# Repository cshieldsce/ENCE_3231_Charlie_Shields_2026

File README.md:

# Embedded Systems Coursework (ENCE 3231)

A small portfolio-style repo of my embedded + hardware design work for class.

## Projects

### 01 — Lab 1: Ultrasonic sensor (timers only)

- **Folder:** `01_lab1_ultrasonic_timers/`
- **What it shows:** timer-driven trigger pulse + measurement cycle; scope + block diagram.
- **Write-up:** `01_lab1_ultrasonic_timers/README.md`

### 02 — CAN board (KiCad)

- **Folder:** `02_can_kicad_board/`
- **What it shows:** CAN interface/board design in KiCad (schematic + PCB).
- **Write-up:** `02_can_kicad_board/README.md`

### 03 — Balancing robot schematic (KiCad)

- **Folder:** `03_balancing_robot_schematic_v1/`
- **What it shows:** system schematic for a 2-wheel balancing robot build.
- **Write-up:** `03_balancing_robot_schematic_v1/README.md`

### 04 — Balancing robot PCB layout (KiCad)

- **Folder:** `04_balancing_robot_pcb_v1/2026_12_2Wheel_Balance_Robot_v1/`
- **What it shows:** PCB layout + 3D renders for the balancing robot.
- **Write-up:** `04_balancing_robot_pcb_v1/README.md`

## Quick open / build

- **KiCad:** open the `*.kicad_pro` file inside a project folder.
- **STM32CubeIDE:** open/import the folder under the lab and build in the IDE (build outputs are ignored).

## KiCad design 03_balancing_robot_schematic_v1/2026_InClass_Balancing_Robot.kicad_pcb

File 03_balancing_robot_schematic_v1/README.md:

# 2-Wheel Balancing Robot — Schematic (v1)

## Open in KiCad

- Open `2026_InClass_Balancing_Robot.kicad_pro`

## Preview

## Export

- PDF: `docs/schematic_guide.pdf`

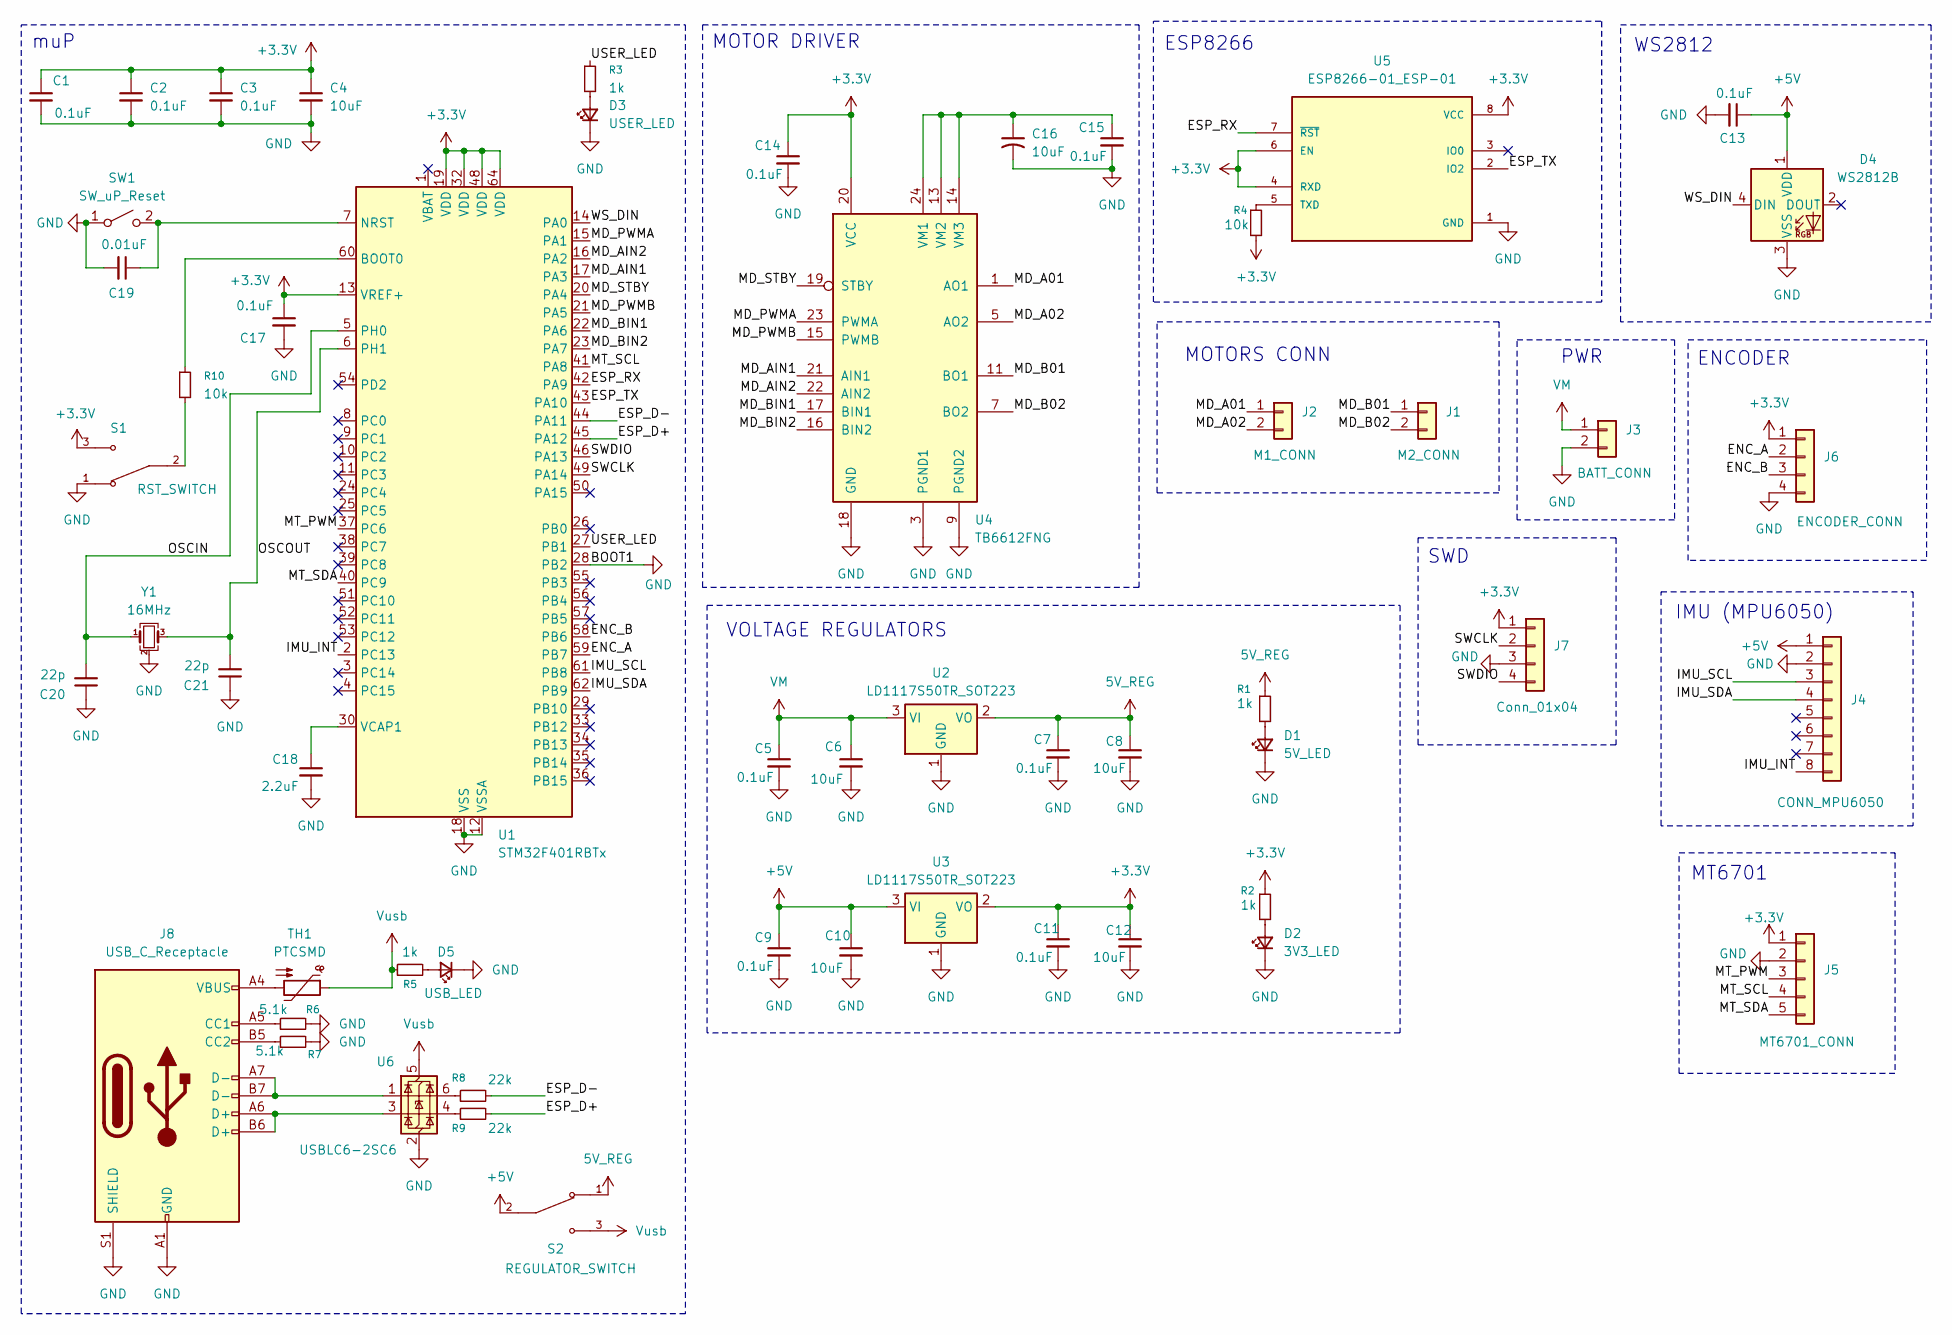
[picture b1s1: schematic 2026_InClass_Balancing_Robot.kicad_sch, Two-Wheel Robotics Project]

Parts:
C1, C2, C3, C5, C7, C9, C11, C13, C14, C15, C17: 0.1uF; C_0805_2012Metric_Pad1.18x1.45mm_HandSolder; Mfr. # KAM21BR71H104JM
C4, C6, C8, C10, C12: 10uF; C_0805_2012Metric_Pad1.18x1.45mm_HandSolder; Mfr. # C2012X5R1A106K085AC
C16: 10uF; C_0805_2012Metric_Pad1.18x1.45mm_HandSolder
C18: 2.2uF; C_0805_2012Metric_Pad1.18x1.45mm_HandSolder; Mfr. # KAM21BR71H104JM
C19: 0.01uF; C_0805_2012Metric_Pad1.18x1.45mm_HandSolder; Mfr. # KAM21BR71H104JM
C20, C21: 22p; C_0805_2012Metric_Pad1.18x1.45mm_HandSolder; Mfr. # KAM21BR71H104JM
D1: 5V_LED; LED_0805_2012Metric_Pad1.15x1.40mm_HandSolder
D2: 3V3_LED; LED_0805_2012Metric_Pad1.15x1.40mm_HandSolder
D3: USER_LED; LED_0805_2012Metric_Pad1.15x1.40mm_HandSolder
D4: WS2812B; LED_WS2812B_PLCC4_5.0x5.0mm_P3.2mm
D5: USB_LED; LED_0805_2012Metric_Pad1.15x1.40mm_HandSolder
J1: M2_CONN; JST_XH_B2B-XH-A_1x02_P2.50mm_Vertical
J2: M1_CONN; JST_XH_B2B-XH-A_1x02_P2.50mm_Vertical
J3: BATT_CONN; JST_XH_B2B-XH-A_1x02_P2.50mm_Vertical
J4: CONN_MPU6050; PinSocket_1x08_P2.54mm_Vertical
J5: MT6701_CONN; JST_XH_B5B-XH-A_1x05_P2.50mm_Vertical
J6: ENCODER_CONN; JST_XH_B4B-XH-A_1x04_P2.50mm_Vertical
J7: Conn_01x04; PinHeader_1x04_P2.54mm_Vertical
J8: USB_C_Receptacle; USB_C_Receptacle_HCTL_HC-TYPE-C-16P-01A
R1, R2, R3, R5: 1k; R_0805_2012Metric_Pad1.20x1.40mm_HandSolder
R4, R10: 10k; R_0805_2012Metric_Pad1.20x1.40mm_HandSolder
R6, R7: 5.1k; R_0805_2012Metric_Pad1.20x1.40mm_HandSolder
R8, R9: 22k; R_0805_2012Metric_Pad1.20x1.40mm_HandSolder
S1: RST_SWITCH; SW_SLW-66527511-SMT-TR; PARTREV 1.01
S2: REGULATOR_SWITCH; SW_SLW-66527511-SMT-TR; PARTREV 1.01
SW1: SW_uP_Reset
TH1: PTCSMD; Fuse_1812_4532Metric
U1: STM32F401RBTx; LQFP-64_10x10mm_P0.5mm; Mfr. # STM32F401RET6
U2, U3: LD1117S50TR_SOT223; SOT-223-3_TabPin2
U4: TB6612FNG; SSOP-24_5.3x8.2mm_P0.65mm
U5: ESP8266-01_ESP-01; PARTREV V1.2
U6: USBLC6-2SC6; SOT-23-6
Y1: 16MHz; Crystal_SMD_Abracon_ABM8G-4Pin_3.2x2.5mm

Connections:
5V_REG: C7.1, C8.1, R1.1, S2.1, U2.2 (VO)
+3.3V: C1.1, C2.1, C3.1, C4.1, C11.1, C12.1, C14.1, C17.1, J5.1, J6.1, J7.1, R2.1, R4.2, S1.3, U1.13 (VREF+), U1.19 (VDD), U1.32 (VDD), U1.48 (VDD), U1.64 (VDD), U3.2 (VO), U4.20 (VCC), U5.4 (RXD), U5.6 (EN), U5.8 (VCC)
+5V: C9.1, C10.1, C13.1, D4.1 (VDD), J4.1, S2.2, U3.3 (VI)
/ENC_A: J6.2, U1.59 (PB7)
/ENC_B: J6.3, U1.58 (PB6)
/ESP_D+: R9.2, U1.45 (PA12)
/ESP_D-: R8.2, U1.44 (PA11)
/ESP_RX: U1.42 (PA9), U5.7 (~RST)
/ESP_TX: U1.43 (PA10), U5.2 (IO2)
/IMU_INT: J4.8, U1.2 (PC13)
/IMU_SCL: J4.3, U1.61 (PB8)
/IMU_SDA: J4.4, U1.62 (PB9)
/MD_A01: J2.1, U4.1 (AO1), U4.2 (AO1)
/MD_A02: J2.2, U4.5 (AO2), U4.6 (AO2)
/MD_AIN1: U1.17 (PA3), U4.21 (AIN1)
/MD_AIN2: U1.16 (PA2), U4.22 (AIN2)
/MD_B01: J1.1, U4.11 (BO1), U4.12 (BO1)
/MD_B02: J1.2, U4.7 (BO2), U4.8 (BO2)
/MD_BIN1: U1.22 (PA6), U4.17 (BIN1)
/MD_BIN2: U1.23 (PA7), U4.16 (BIN2)
/MD_PWMA: U1.15 (PA1), U4.23 (PWMA)
/MD_PWMB: U1.21 (PA5), U4.15 (PWMB)
/MD_STBY: U1.20 (PA4), U4.19 (STBY)
/MT_PWM: J5.3, U1.37 (PC6)
/MT_SCL: J5.4, U1.41 (PA8)
/MT_SDA: J5.5, U1.40 (PC9)
/OSCIN: C20.2, U1.5 (PH0), Y1.1
/OSCOUT: C21.2, U1.6 (PH1), Y1.3
/SWCLK: J7.2, U1.49 (PA14)
/SWDIO: J7.4, U1.46 (PA13)
/USER_LED: R3.1, U1.27 (PB1)
/WS_DIN: D4.4 (DIN), U1.14 (PA0)
GND: C1.2, C2.2, C3.2, C4.2, C5.2, C6.2, C7.2, C8.2, C9.2, C10.2, C11.2, C12.2, C13.2, C14.2, C15.2, C16.2, C17.2, C18.2, C19.2, C20.1, C21.1, D1.1 (K), D2.1 (K), D3.1 (K), D4.3 (VSS), D5.1 (K), J3.2, J4.2, J5.2, J6.4, J7.3, J8.A1 (GND), J8.A12 (GND), J8.B1 (GND), J8.B12 (GND), J8.S1 (SHIELD), R6.2, R7.2, S1.1, SW1.1 (A), U1.12 (VSSA), U1.18 (VSS), U1.28 (PB2), U1.31 (VSS), U1.47 (VSS), U1.63 (VSS), U2.1 (GND), U3.1 (GND), U4.3 (PGND1), U4.4 (PGND1), U4.9 (PGND2), U4.10 (PGND2), U4.18 (GND), U5.1 (GND), U6.2 (GND), Y1.2 (G), Y1.4 (G)
unnamed: D1.2 (A), R1.2
unnamed: D2.2 (A), R2.2
unnamed: D3.2 (A), R3.2
unnamed: D5.2 (A), R5.2
unnamed: J8.A5 (CC1), R6.1
unnamed: J8.B5 (CC2), R7.1
unnamed: J8.A6 (D+), J8.B6 (D+), U6.3 (I/O2)
unnamed: J8.A7 (D-), J8.B7 (D-), U6.1 (I/O1)
unnamed: J8.A4 (VBUS), J8.A9 (VBUS), J8.B4 (VBUS), J8.B9 (VBUS), TH1.2
unnamed: R8.1, U6.6 (I/O1)
unnamed: R9.1, U6.4 (I/O2)
unnamed: R10.2, S1.2
unnamed: C19.1, SW1.2 (B), U1.7 (NRST)
unnamed: R10.1, U1.60 (BOOT0)
unnamed: C18.1, U1.30 (VCAP1)
unnamed: C15.1, C16.1, U4.13 (VM2), U4.14 (VM3), U4.24 (VM1)
unnamed: R4.1, U5.5 (TXD)
VM: C5.1, C6.1, J3.1, U2.3 (VI)
Vusb: R5.1, S2.3, TH1.1, U6.5 (VBUS)

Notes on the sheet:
MT6701
WS2812
PWR
ESP8266
ENCODER
IMU (MPU6050)
muP
VOLTAGE REGULATORS
MOTOR DRIVER
SWD
MOTORS CONN

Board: 2 copper layers, 55 parts (0 on the bottom side), 52 nets, no tracks yet.

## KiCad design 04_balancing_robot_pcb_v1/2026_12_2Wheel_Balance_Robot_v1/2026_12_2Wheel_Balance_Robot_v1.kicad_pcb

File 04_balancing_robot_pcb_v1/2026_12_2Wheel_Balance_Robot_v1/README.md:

# 2-Wheel Balancing Robot — PCB Project (KiCad)

## Open in KiCad

- Open `2026_12_2Wheel_Balance_Robot_v1.kicad_pro`

## 3D Views

## Outputs

- BOM: `BOM/`
- Gerbers: `gerber/`

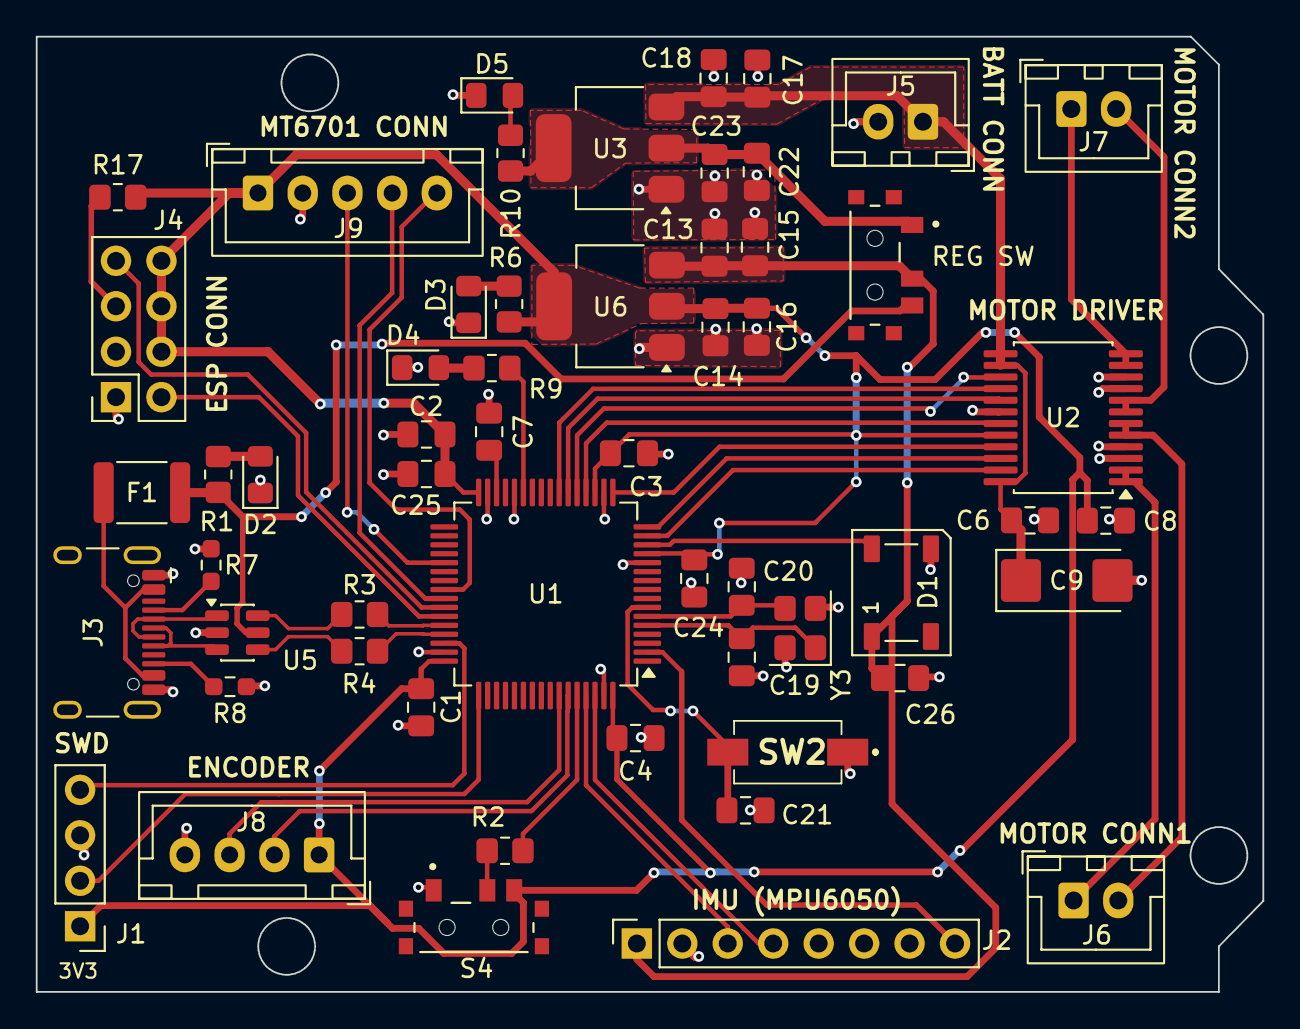
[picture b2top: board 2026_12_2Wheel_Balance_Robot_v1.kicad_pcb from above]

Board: 2 copper layers, 68.6 x 53.4 mm, 56 parts (0 on the bottom side), 51 nets.

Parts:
C1, C2, C3, C4, C6, C8, C13, C14, C17, C22, C24, C26: 0.1uF; C_0805_2012Metric_Pad1.18x1.45mm_HandSolder
C7: 2.2uF; C_0805_2012Metric_Pad1.18x1.45mm_HandSolder
C9: 10uF; CP_EIA-6032-28_Kemet-C_HandSolder
C15, C16, C18, C23, C25: 10uF; C_0805_2012Metric_Pad1.18x1.45mm_HandSolder
C19, C20: 22p; C_0805_2012Metric_Pad1.18x1.45mm_HandSolder
C21: 0.01uF; C_0805_2012Metric_Pad1.18x1.45mm_HandSolder
D1: WS2812B; LED_WS2812B_PLCC4_5.0x5.0mm_P3.2mm
D2: USB_LED; LED_0805_2012Metric_Pad1.15x1.40mm_HandSolder
D3: 3V3_LED; LED_0805_2012Metric_Pad1.15x1.40mm_HandSolder
D4: USER_LED; LED_0805_2012Metric_Pad1.15x1.40mm_HandSolder
D5: 5V_LED; LED_0805_2012Metric_Pad1.15x1.40mm_HandSolder
F1: PTCSMD; Fuse_1812_4532Metric
J1: Conn_01x04; PinHeader_1x04_P2.54mm_Vertical
J2: CONN_MPU6050; PinSocket_1x08_P2.54mm_Vertical
J3: USB_C_Receptacle_USB2.0_14P; USB_C_Receptacle_HCTL_HC-TYPE-C-16P-01A
J4: ESP_Conn; PinSocket_2x04_P2.54mm_Vertical
J5: BATT_CONN; JST_XH_B2B-XH-A_1x02_P2.50mm_Vertical
J6: M1_CONN; JST_XH_B2B-XH-A_1x02_P2.50mm_Vertical
J7: M2_CONN; JST_XH_B2B-XH-A_1x02_P2.50mm_Vertical
J8: ENCODER_CONN; JST_XH_B4B-XH-A_1x04_P2.50mm_Vertical
J9: MT6701_CONN; JST_XH_B5B-XH-A_1x05_P2.50mm_Vertical
R1, R6, R9, R10: 1k; R_0805_2012Metric_Pad1.20x1.40mm_HandSolder
R2, R17: 10k; R_0805_2012Metric_Pad1.20x1.40mm_HandSolder
R3, R4: 22R; R_0805_2012Metric_Pad1.20x1.40mm_HandSolder
R7, R8: 5.1k; R_0603_1608Metric_Pad0.98x0.95mm_HandSolder
REG SW: REGULATOR_SWITCH; SW_SLW-66527511-SMT-TR
S4: RST_SWITCH; SW_SLW-66527511-SMT-TR
SW2: SW_uP_Reset
U1: STM32F401RBTx; LQFP-64_10x10mm_P0.5mm
U2: TB6612FNG; SSOP-24_5.3x8.2mm_P0.65mm
U3: LD1117S50TR_SOT223; SOT-223-3_TabPin2
U5: USBLC6-2SC6; SOT-23-6
U6: LD1117S33TR_SOT223; SOT-223-3_TabPin2
Y3: 16MHz; Crystal_SMD_Abracon_ABM8G-4Pin_3.2x2.5mm

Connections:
5V_REG: C22.1, C23.1, R10.2, REG SW.1, U3.2 (VO)
+3.3V: C1.1, C2.1, C3.1, C4.1, C8.1, C14.1, C16.1, C24.1, C25.1, J1.1, J4.4, J4.6, J4.8, J8.1, J9.1, R6.2, R17.1, S4.3, U1.13 (VREF+), U1.19 (VDD), U1.32 (VDD), U1.48 (VDD), U1.64 (VDD), U2.20 (VCC), U6.2 (VO)
+5V: C13.1, C15.1, C26.2, D1.1 (VDD), J2.1, REG SW.2, U6.3 (VI)
/BOOT0: R2.2, U1.60 (BOOT0)
/CONN_D+: R4.1, U5.4 (I/O2)
/CONN_D-: R3.1, U5.6 (I/O1)
/ENC_A: J8.2, U1.59 (PB7)
/ENC_B: J8.3, U1.58 (PB6)
/ESD_D+: R4.2, U1.45 (USB_OTG_FS_DP)
/ESD_D-: R3.2, U1.44 (USB_OTG_FS_DM)
/ESP_RX: J4.7, U1.42 (USART1_TX)
/ESP_TX: J4.2, U1.43 (USART1_RX)
/IMU_INT: J2.8, U1.2 (PC13)
/IMU_SCL: J2.3, U1.61 (I2C1_SCL)
/IMU_SDA: J2.4, U1.62 (I2C1_SDA)
/MD_AIN1: U1.17 (PA3), U2.21 (AIN1)
/MD_AIN2: U1.16 (PA2), U2.22 (AIN2)
/MD_AO1: J6.1, U2.1 (AO1), U2.2 (AO1)
/MD_AO2: J6.2, U2.5 (AO2), U2.6 (AO2)
/MD_BIN1: U1.22 (PA6), U2.17 (BIN1)
/MD_BIN2: U1.23 (PA7), U2.16 (BIN2)
/MD_BO1: J7.1, U2.11 (BO1), U2.12 (BO1)
/MD_BO2: J7.2, U2.7 (BO2), U2.8 (BO2)
/MD_PWMA: U1.15 (TIM2_CH2), U2.23 (PWMA)
/MD_PWMB: U1.21 (TIM2_CH1), U2.15 (PWMB)
/MD_STBY: U1.20 (PA4), U2.19 (STBY)
/MT_PWM: J9.3, U1.37 (PC6)
/MT_SCL: J9.4, U1.41 (I2C3_SCL)
/MT_SDA: J9.5, U1.40 (I2C3_SDA)
/OSCIN: C19.2, U1.5 (RCC_OSC_IN), Y3.1
/OSCOUT: C20.2, U1.6 (RCC_OSC_OUT), Y3.3
/RESET: C21.1, SW2.2 (B), U1.7 (NRST)
/SWCLK: J1.2, U1.49 (SYS_JTCK-SWCLK)
/SWDIO: J1.4, U1.46 (SYS_JTMS-SWDIO)
/USB_D+: J3.A6 (D+), J3.B6 (D+), U5.3 (I/O2)
/USB_D-: J3.A7 (D-), J3.B7 (D-), U5.1 (I/O1)
/USER_LED: R9.2, U1.27 (PB1)
/WS_DIN: D1.4 (DIN), U1.14 (TIM5_CH1)
GND: C1.2, C2.2, C3.2, C4.2, C6.2, C7.2, C8.2, C9.2, C13.2, C14.2, C15.2, C16.2, C17.2, C18.2, C19.1, C20.1, C21.2, C22.2, C23.2, C24.2, C25.2, C26.1, D1.3 (VSS), D2.1 (K), D3.1 (K), D4.1 (K), D5.1 (K), J1.3, J2.2, J3.A1 (GND), J3.A12 (GND), J3.B1 (GND), J3.B12 (GND), J3.SH (SHIELD), J4.1, J5.2, J8.4, J9.2, R7.1, R8.2, S4.1, SW2.1 (A), U1.12 (VSSA), U1.18 (VSS), U1.28 (PB2), U1.31 (VSS), U1.47 (VSS), U1.63 (VSS), U2.3 (PGND1), U2.4 (PGND1), U2.9 (PGND2), U2.10 (PGND2), U2.18 (GND), U3.1 (GND), U5.2 (GND), U6.1 (GND), Y3.2, Y3.4
unnamed: D2.2 (A), R1.1
unnamed: D3.2 (A), R6.1
unnamed: D4.2 (A), R9.1
unnamed: D5.2 (A), R10.1
unnamed: F1.1, J3.A4 (VBUS), J3.A9 (VBUS), J3.B4 (VBUS), J3.B9 (VBUS)
unnamed: J3.A5 (CC1), R7.2
unnamed: J3.B5 (CC2), R8.1
unnamed: J4.5, R17.2
unnamed: R2.1, S4.2
unnamed: C7.1, U1.30 (VCAP1)
VM: C6.1, C9.1, C17.1, C18.1, J5.1, U2.13 (VM2), U2.14 (VM3), U2.24 (VM1), U3.3 (VI)
Vusb: F1.2, R1.2, REG SW.3, U5.5 (VBUS)

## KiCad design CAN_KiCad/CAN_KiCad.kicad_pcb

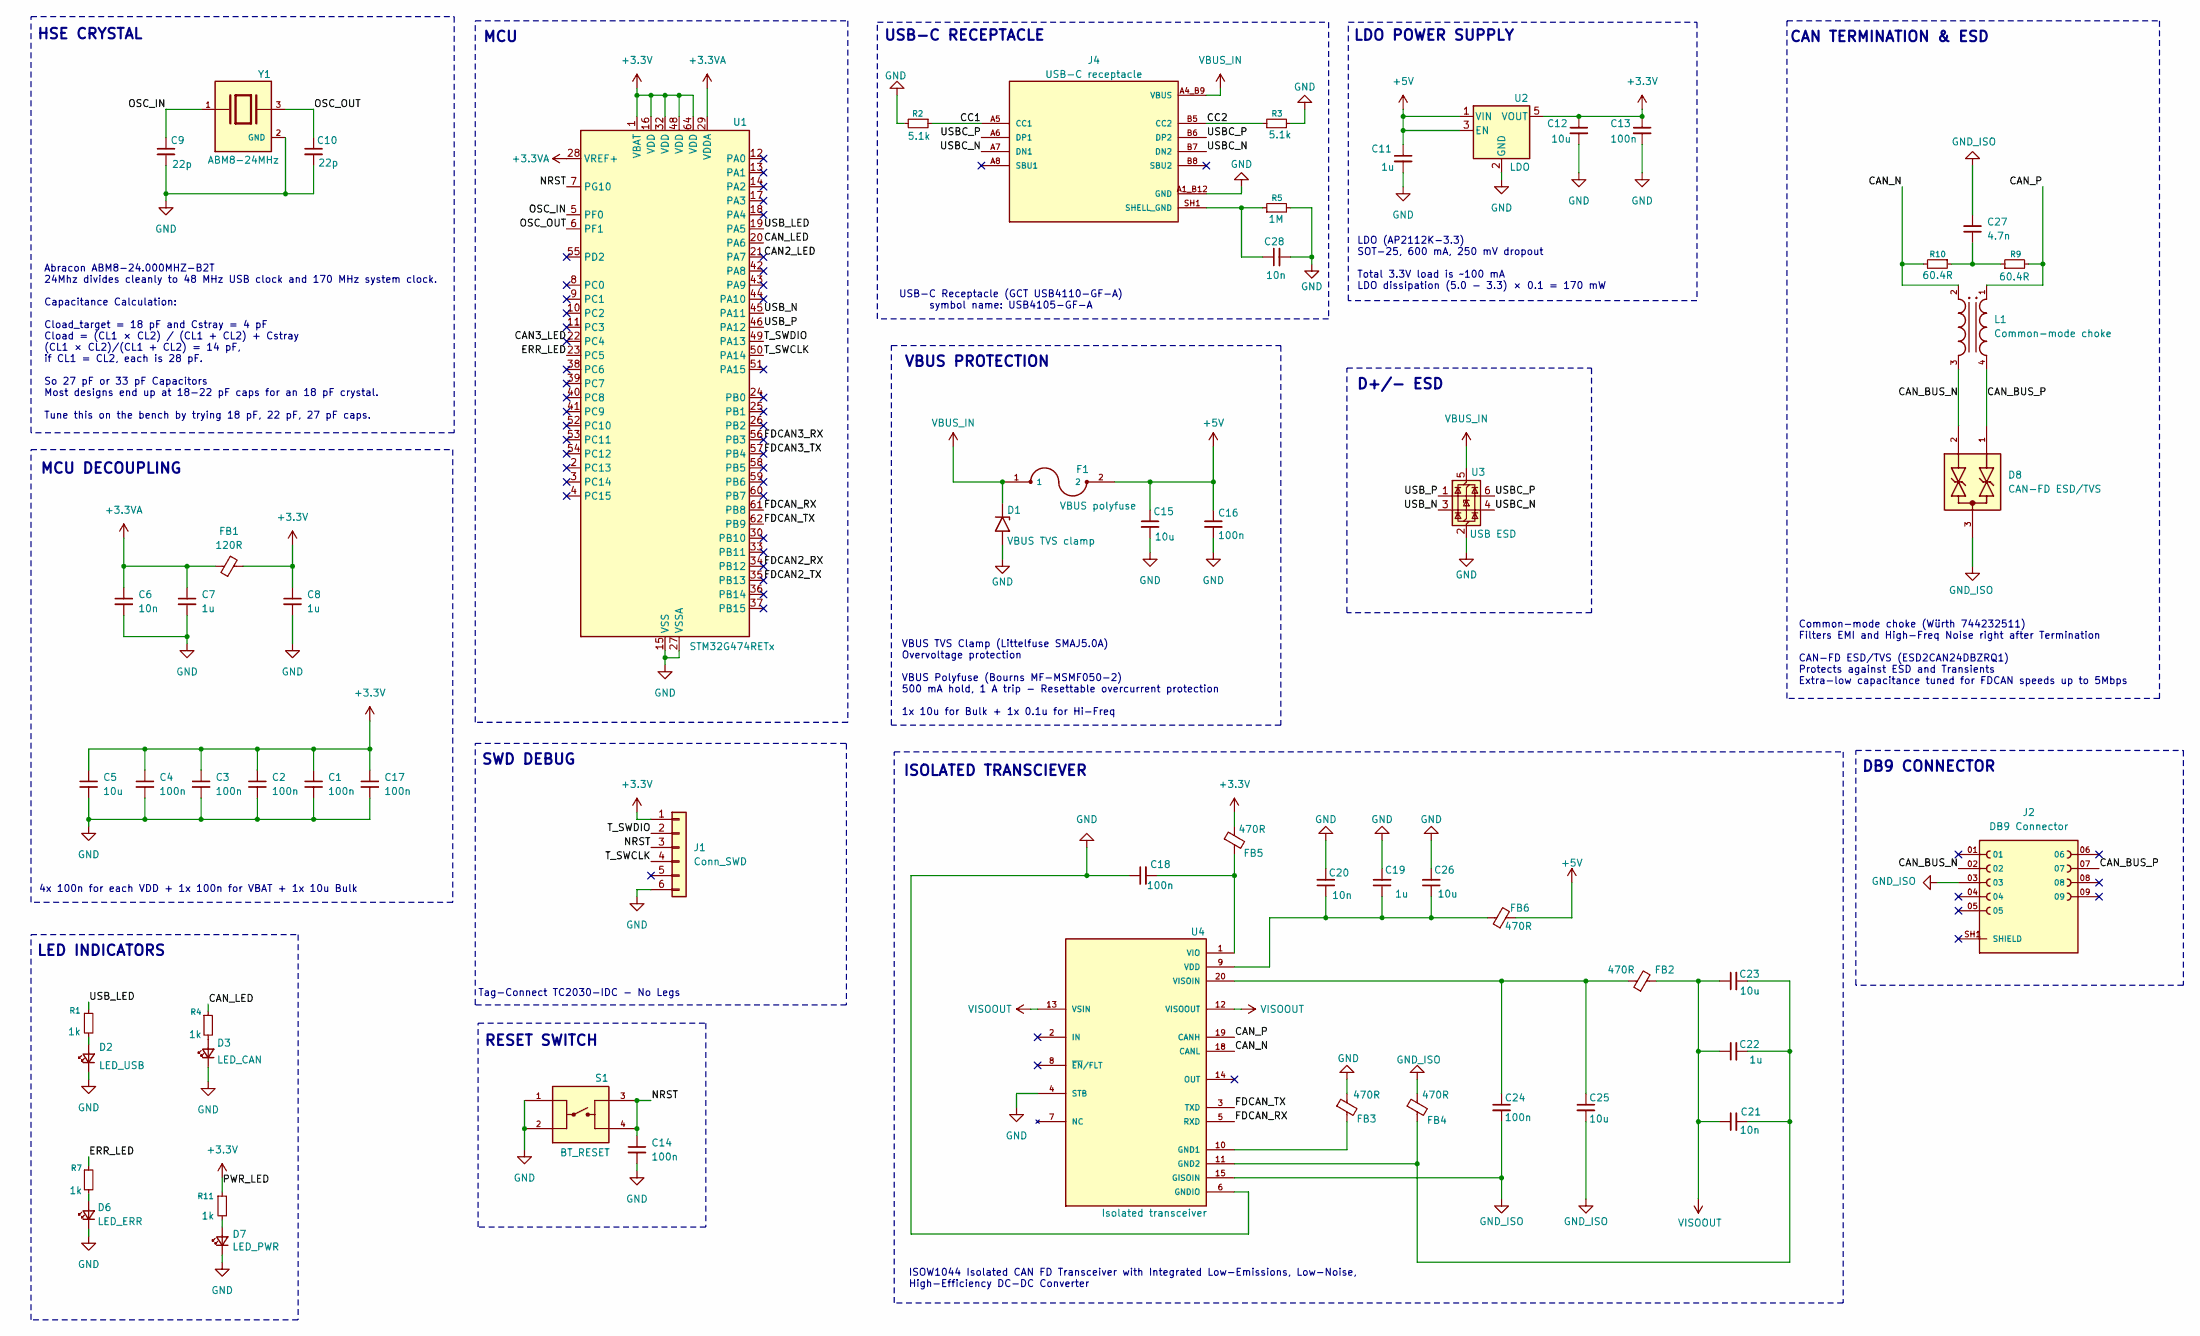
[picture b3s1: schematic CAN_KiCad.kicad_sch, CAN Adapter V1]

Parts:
C1, C2, C3, C4, C13, C14, C16, C17, C18, C24: 100n; C_0402_1005Metric_Pad0.74x0.62mm_HandSolder
C5, C12, C15, C23, C25, C26: 10u; C_0805_2012Metric_Pad1.18x1.45mm_HandSolder
C6, C20, C21, C28: 10n; C_0402_1005Metric_Pad0.74x0.62mm_HandSolder
C7, C8, C11, C19, C22: 1u; C_0603_1608Metric_Pad1.08x0.95mm_HandSolder
C9, C10: 22p; C_0402_1005Metric_Pad0.74x0.62mm_HandSolder
C27: 4.7n; C_0402_1005Metric_Pad0.74x0.62mm_HandSolder
D1: VBUS TVS clamp; D_SMA
D2: LED_USB; LED_0603_1608Metric_Pad1.05x0.95mm_HandSolder
D3: LED_CAN; LED_0603_1608Metric_Pad1.05x0.95mm_HandSolder
D6: LED_ERR; LED_0603_1608Metric_Pad1.05x0.95mm_HandSolder
D7: LED_PWR; LED_0603_1608Metric_Pad1.05x0.95mm_HandSolder
D8: CAN-FD ESD/TVS; SOT95P237X112-3N; PARTREV C
F1: VBUS polyfuse; FUSM4632X85
FB1: 120R; L_0603_1608Metric_Pad1.05x0.95mm_HandSolder
FB2, FB3, FB4, FB5, FB6: 470R; L_0603_1608Metric_Pad1.05x0.95mm_HandSolder
J1: Conn_SWD; PinHeader_1x06_P2.54mm_Vertical
J2: DB9 Connector; AMPHENOL_L77SDE09SA4CH4F; PARTREV 3
J4: USB-C receptacle; GCT_USB4105-GF-A; PARTREV B4
L1: Common-mode choke; WE-SL5_HC
R1, R4, R7, R11: 1k; R_0603_1608Metric_Pad0.98x0.95mm_HandSolder
R2, R3: 5.1k; R_0402_1005Metric_Pad0.72x0.64mm_HandSolder
R5: 1M; R_0402_1005Metric_Pad0.72x0.64mm_HandSolder
R9, R10: 60.4R; R_0603_1608Metric_Pad0.98x0.95mm_HandSolder
S1: BT_RESET; SW_PTS525SM15SMTR2LFS; PARTREV NA
U1: STM32G474RETx; LQFP-64_10x10mm_P0.5mm
U2: LDO; SOT-23-5
U3: USB ESD; SOT-23-6
U4: Isolated transceiver; XCVR_ISOW1044BDFMR; PARTREV A
Y1: ABM8-24MHz; XTAL_ABM8-24.000MHZ-B2-T; PARTREV 44041

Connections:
+3.3V: C1.1, C2.1, C3.1, C4.1, C5.1, C8.1, C12.1, C13.1, C17.1, FB1.2, FB5.1, J1.1, R11.1, U1.1 (VBAT), U1.16 (VDD), U1.32 (VDD), U1.48 (VDD), U1.64 (VDD), U2.5 (VOUT)
+3.3VA: C6.1, C7.1, FB1.1, U1.28 (VREF+), U1.29 (VDDA)
+5V: C11.1, C15.1, C16.1, F1.2, FB6.2, U2.1 (VIN), U2.3 (EN)
/CAN2_LED: U1.21 (PA7)
/CAN3_LED: U1.22 (PC4)
/CAN_BUS_N: D8.2, J2.02, L1.3
/CAN_BUS_P: D8.1, J2.07, L1.4
/CAN_LED: R4.1, U1.20 (PA6)
/CAN_N: L1.2, R10.2, U4.18 (CANL)
/CAN_P: L1.1, R9.2, U4.19 (CANH)
/CC1: J4.A5 (CC1), R2.1
/CC2: J4.B5 (CC2), R3.1
/ERR_LED: R7.1, U1.23 (PC5)
/FDCAN2_RX: U1.34 (PB12)
/FDCAN2_TX: U1.35 (PB13)
/FDCAN3_RX: U1.56 (PB3)
/FDCAN3_TX: U1.57 (PB4)
/FDCAN_RX: U1.61 (PB8), U4.5 (RXD)
/FDCAN_TX: U1.62 (PB9), U4.3 (TXD)
/NRST: C14.1, J1.3, S1.3, S1.4, U1.7 (PG10)
/OSC_IN: C9.1, U1.5 (PF0), Y1.1
/OSC_OUT: C10.1, U1.6 (PF1), Y1.3
/T_SWCLK: J1.4, U1.50 (PA14)
/T_SWDIO: J1.2, U1.49 (PA13)
/USBC_N: J4.A7 (DN1), J4.B7 (DN2), U3.4 (I/O2)
/USBC_P: J4.A6 (DP1), J4.B6 (DP2), U3.6 (I/O1)
/USB_LED: R1.1, U1.19 (PA5)
/USB_N: U1.45 (PA11), U3.3 (I/O2)
/USB_P: U1.46 (PA12), U3.1 (I/O1)
GND: C1.2, C2.2, C3.2, C4.2, C5.2, C6.2, C7.2, C8.2, C9.2, C10.2, C11.2, C12.2, C13.2, C14.2, C15.2, C16.2, C17.2, C18.1, C19.2, C20.2, C26.2, C28.2, D1.2 (A2), D2.1 (K), D3.1 (K), D6.1 (K), D7.1 (K), FB3.1, J1.6, J4.A1_B12 (GND), J4.B1_A12 (GND), R2.2, R3.2, R5.2, S1.1, S1.2, U1.15 (VSS), U1.27 (VSSA), U1.31 (VSS), U1.47 (VSS), U1.63 (VSS), U2.2 (GND), U3.2 (GND), U4.4 (STB), U4.6 (GNDIO), Y1.2 (GND), Y1.4 (GND)
GND_ISO: C24.2, C25.2, C27.2, D8.3, FB4.1, J2.03, U4.15 (GISOIN), U4.16 (GISOIN), U4.17 (GISOIN)
unnamed: C27.1, R9.1, R10.1
unnamed: D2.2 (A), R1.2
unnamed: D3.2 (A), R4.2
unnamed: D6.2 (A), R7.2
unnamed: D7.2 (A), R11.2
unnamed: FB3.2, U4.10 (GND1)
unnamed: C21.2, C22.2, C23.2, FB4.2, U4.11 (GND2)
unnamed: C19.1, C20.1, C26.1, FB6.1, U4.9 (VDD)
unnamed: C18.2, FB5.2, U4.1 (VIO)
unnamed: C24.1, C25.1, FB2.1, U4.20 (VISOIN)
SHELL_GND: C28.1, J4.SH1 (SHELL_GND), J4.SH2 (SHELL_GND), J4.SH3 (SHELL_GND), J4.SH4 (SHELL_GND), R5.1
VBUS_IN: D1.1 (A1), F1.1, J4.A4_B9 (VBUS), J4.B4_A9 (VBUS), U3.5 (VBUS)
VISOOUT: C21.1, C22.1, C23.1, FB2.2, U4.12 (VISOOUT), U4.13 (VSIN)

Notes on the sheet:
LED INDICATORS
SWD DEBUG
RESET SWITCH
HSE CRYSTAL
ISOLATED TRANSCIEVER
CAN TERMINATION & ESD
USB-C Receptacle (GCT USB4110-GF-A) symbol name: USB4105-GF-A
MCU
LDO (AP2112K-3.3) SOT-25, 600 mA, 250 mV dropout Total 3.3V load is ~100 mA LDO dissipation (5.0 - 3.3) × 0.1 = 170 mW
VBUS PROTECTION
Tag-Connect TC2030-IDC - No Legs
4x 100n for each VDD + 1x 100n for VBAT + 1x 10u Bulk
Abracon ABM8-24.000MHZ-B2T 24Mhz divides cleanly to 48 MHz USB clock and 170 MHz system clock. Capacitance Calculation: Cload_target = 18 pF and Cstray = 4 pF Cload = (CL1 × CL2) / (CL1 + CL2) + Cstray (CL1 × CL2)/(CL1 + CL2) = 14 pF, if CL1 = CL2, each is 28 pF. So 27 pF or 33 pF Capacitors Most d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
MCU DECOUPLING
D+/- ESD
VBUS TVS Clamp (Littelfuse SMAJ5.0A) Overvoltage protection VBUS Polyfuse (Bourns MF-MSMF050-2) 500 mA hold, 1 A trip - Resettable overcurrent protection 1x 10u for Bulk + 1x 0.1u for Hi-Freq
LDO POWER SUPPLY
USB-C RECEPTACLE
ISOW1044 Isolated CAN FD Transceiver with Integrated Low-Emissions, Low-Noise, High-Efficiency DC-DC Converter
DB9 CONNECTOR
Common-mode choke (Würth 744232511) Filters EMI and High-Freq Noise right after Termination CAN-FD ESD/TVS (ESD2CAN24DBZRQ1) Protects against ESD and Transients Extra-low capacitance tuned for FDCAN speeds up to 5Mbps

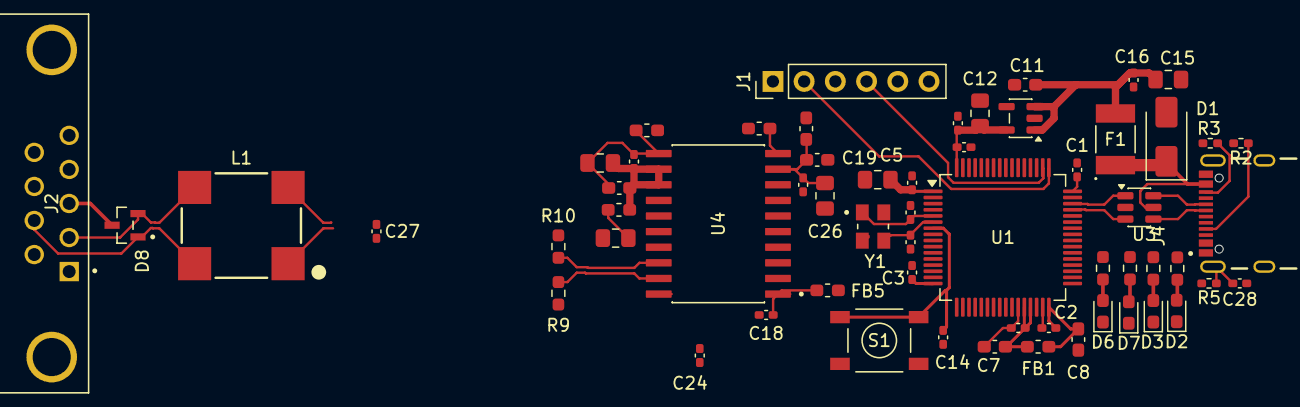
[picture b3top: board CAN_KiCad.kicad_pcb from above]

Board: 2 copper layers, 60 parts (0 on the bottom side), 38 nets.

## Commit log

2026-04-16 add lab1
2026-04-16 add CubeIDE project, gitignore, and lab README
    - Import Week3_Class1_Timer1_Pulse STM32CubeIDE project (F407VG); 10us
    TRIG pulse on TIM2 CH1 gated by TIM1 60ms tick is working; echo
    capture / distance calc still TODO.
    - Add .gitignore covering Debug/Release build output and Eclipse cruft
    while keeping .project/.cproject/.settings/.ioc/*.ld so the project
    can be cloned and reimported as-is.
2026-04-23 Add robot schematic
2026-04-23 Update schematic picture
2026-04-23 Upload schematic png and README.md
2026-04-23 Add updated schematic
2026-04-29 Add Phils Lab Tutorial project
2026-05-05 upload gerber
2026-05-05 update gerber
2026-05-06 add drill files
2026-05-14 reorganize repo
